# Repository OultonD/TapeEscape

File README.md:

# TapeEscape

Codebase and Schematics for Arduino based props

[Outside the March](https://outsidethemarch.ca/)

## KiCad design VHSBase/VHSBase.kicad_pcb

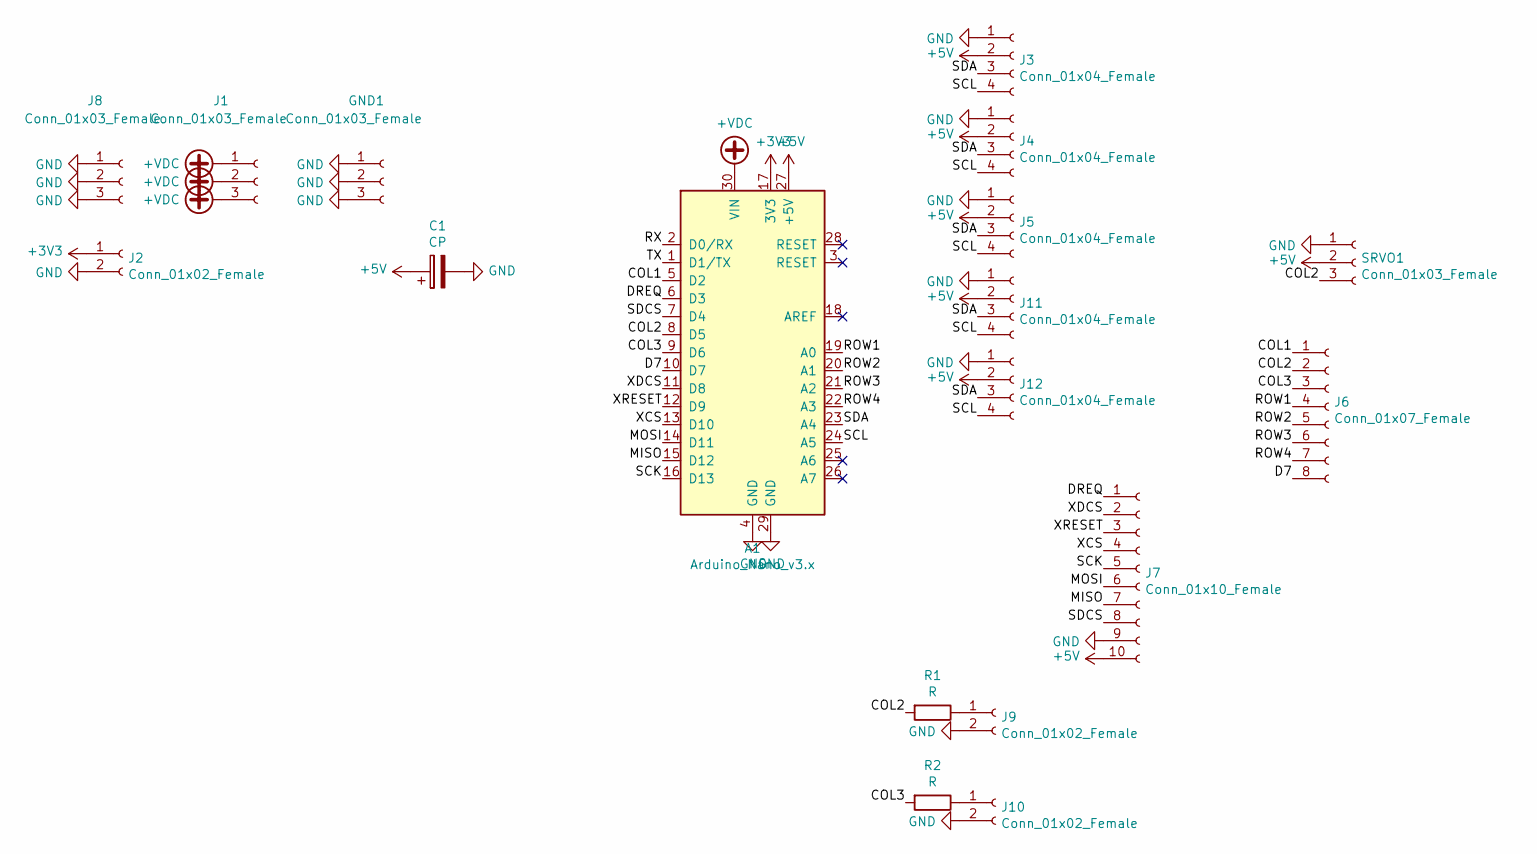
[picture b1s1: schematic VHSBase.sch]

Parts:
A1: Arduino_Nano_v3.x; Arduino_Nano
C1: CP; CP_Radial_D5.0mm_P2.00mm
GND1: Conn_01x03_Female; Pin_Header_Straight_1x03_Pitch2.54mm
J1, J8: Conn_01x03_Female; Pin_Header_Straight_1x03_Pitch2.54mm
J2, J9, J10: Conn_01x02_Female; Pin_Header_Straight_1x02_Pitch2.54mm
J3, J4, J5, J11, J12: Conn_01x04_Female; Pin_Header_Straight_1x04_Pitch2.54mm
J6: Conn_01x07_Female; Pin_Header_Straight_1x08_Pitch2.54mm
J7: Conn_01x10_Female; Pin_Header_Straight_1x10_Pitch2.54mm
R1, R2: R; R_Axial_DIN0309_L9.0mm_D3.2mm_P2.54mm_Vertical
SRVO1: Conn_01x03_Female; Pin_Header_Straight_1x03_Pitch2.54mm

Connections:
+3V3: A1.17 (3V3), J2.1
+5V: A1.27 (+5V), C1.1, J3.2, J4.2, J5.2, J7.10, J11.2, J12.2, SRVO1.2
+VDC: A1.30 (VIN), J1.1, J1.2, J1.3
/COL1: A1.5 (D2), J6.1
/COL2: A1.8 (D5), J6.2, R1.2, SRVO1.3
/COL3: A1.9 (D6), J6.3, R2.2
/D7: A1.10 (D7), J6.8
/DREQ: A1.6 (D3), J7.1
/MISO: A1.15 (D12), J7.7
/MOSI: A1.14 (D11), J7.6
/ROW1: A1.19 (A0), J6.4
/ROW2: A1.20 (A1), J6.5
/ROW3: A1.21 (A2), J6.6
/ROW4: A1.22 (A3), J6.7
/RX: A1.2 (D0/RX)
/SCK: A1.16 (D13), J7.5
/SCL: A1.24 (A5), J3.4, J4.4, J5.4, J11.4, J12.4
/SDA: A1.23 (A4), J3.3, J4.3, J5.3, J11.3, J12.3
/SDCS: A1.7 (D4), J7.8
/TX: A1.1 (D1/TX)
/XCS: A1.13 (D10), J7.4
/XDCS: A1.11 (D8), J7.2
/XRESET: A1.12 (D9), J7.3
GND: A1.4 (GND), A1.29 (GND), C1.2, GND1.1, GND1.2, GND1.3, J2.2, J3.1, J4.1, J5.1, J7.9, J8.1, J8.2, J8.3, J9.2, J10.2, J11.1, J12.1, SRVO1.1
unnamed: J9.1, R1.1
unnamed: J10.1, R2.1

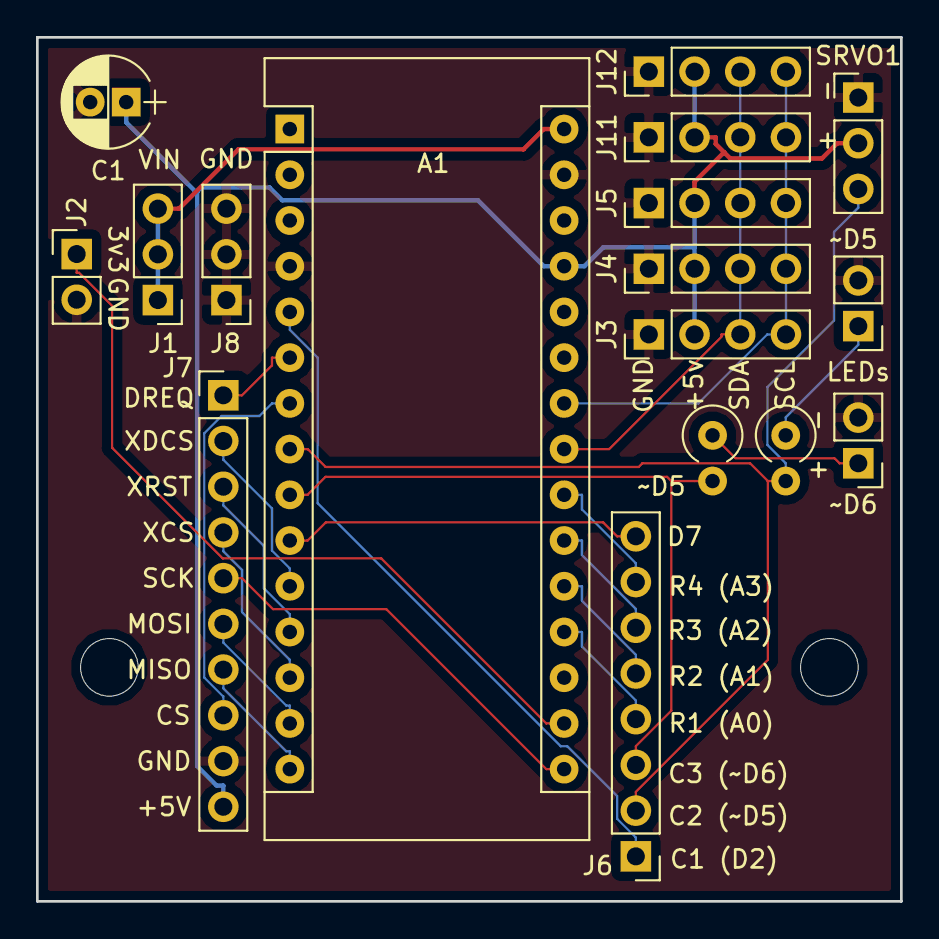
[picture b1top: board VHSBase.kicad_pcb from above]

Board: 2 copper layers, 48.0 x 48.0 mm, 19 parts (0 on the bottom side), 24 nets.

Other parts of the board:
H1, H2: MountingHole_3.2mm_M3

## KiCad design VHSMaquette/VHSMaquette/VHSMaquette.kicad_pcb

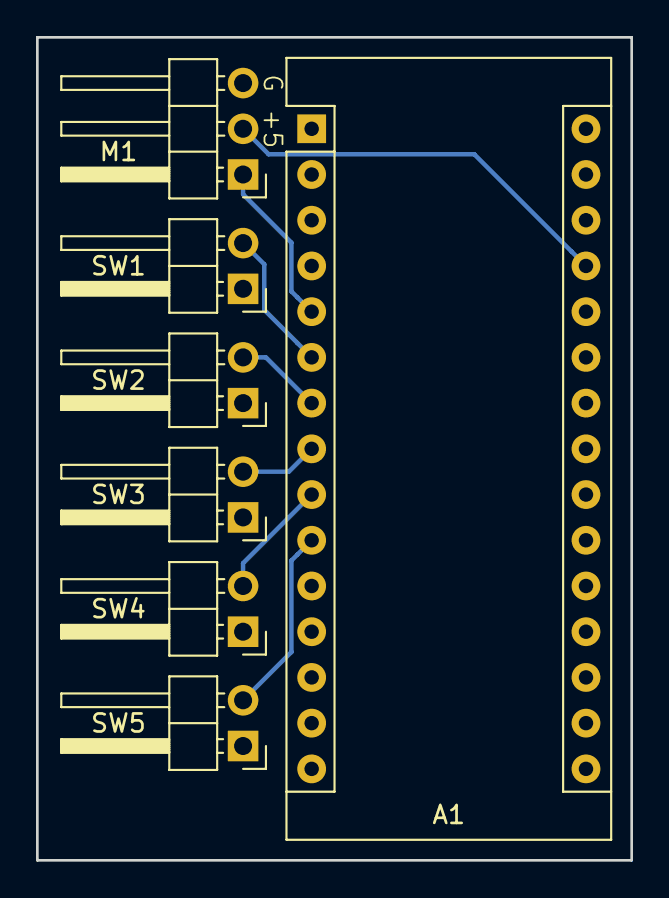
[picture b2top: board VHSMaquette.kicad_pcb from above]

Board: 2 copper layers, 33.0 x 45.7 mm, 7 parts (0 on the bottom side), 8 nets.

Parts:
A1: Arduino_Nano_v3.x; Arduino_Nano
M1: Motor_Servo; Pin_Header_Angled_1x03_Pitch2.54mm
SW1, SW2, SW3, SW4, SW5: SW_Reed; Pin_Header_Angled_1x02_Pitch2.54mm

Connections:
+5V: A1.27, M1.2
GND: A1.4, A1.29, M1.3, SW1.1, SW2.1, SW3.1, SW4.1, SW5.1
unnamed: A1.5, M1.1
unnamed: A1.6, SW1.2
unnamed: A1.7, SW2.2
unnamed: A1.8, SW3.2
unnamed: A1.9, SW4.2
unnamed: A1.10, SW5.2

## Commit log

2019-04-12 init
2019-04-17 Updated question strings
2019-04-17 Puzzle code init
2019-04-17 new puzzle code
2019-04-19 Tested and fixed LED code for buttons
2019-04-29 Memory efficency
2019-04-29 Final prototype code
2019-04-30 Working prototype code
2019-05-07 updated code for new functionality: play/rwd/ffw/eject
2019-05-07 Updated to revision 2.2
2019-05-08 Listed 3rd party libraries
2019-05-08 added display and encoder functions
2019-05-09 Answerkey bugfixing
2019-05-09 added playback function
2019-05-11 new diagnostic beeps
2019-05-11 inverted logic
2019-05-12 Cleaning up comments
2019-05-12 Added schematic
2019-05-12 Create LICENSE
2019-05-12 Added hangup function with *
2019-05-12 fixed Path 0 bug
2019-05-12 Added scrolling of long film titles
2019-05-12 Added lockout for buttons
2019-05-12 fixed bug for scrolling titles
2019-05-12 added example isadora file
2019-05-13 Added usage writeup
2019-05-13 Working prototype
2019-05-14 Working AM FM switch, refactoring loop
2019-05-14 update writeup
2019-05-15 Switch to 9600 baud to fix a bug
2019-05-15 Added Writeup
2019-05-15 Working on/off button, RAM optimization
2019-05-15 New playback helper function
2019-05-15 Fixed static, updated to reflect 8 character naming limitation
2019-05-18 Added button lockout functionality for p/r/f/e
2019-05-18 refactored mp3player setup
2019-05-18 volume change
2019-05-19 added failure sound if wrong tree-quence was pressed
2019-05-20 added writeup of required MP3s on the SD card
2019-05-26 Code base for delivered props
2019-05-27 Add documentation pdf
2019-07-04 Update VHSEliza.ino
    Win/Loose Language changed
2019-07-08 Volume adjustment, fixed buttons, new led flicker
2019-07-09 Swapped ffwd and rewind buttons
